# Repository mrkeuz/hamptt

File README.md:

Ham PTT
=======

Bluetooth PTT switch for ham radio transmitters like Baofeng UV-5R.  
Board helps to control transmitter from PC.

Motivation
----------

Testing of UART interface showed unstable connection. During transmit via UART an usb-ttl 
chip periodically crashes and stops working. Cause is some radio strong interference 
on USB cable. So Bluetooth serial protocol stack (SSP) chosen instead.

Schematic
---------

Host -> (Bluetooth) -> Esp-32 Arduino -> Relay -> Transmitter PTT button

* Hardware

    - Host PC with Bluetooth (tested Ubuntu 20.04)
    - Esp32 DevKit v1 (or similar esp32)
    - Relay shield
    - Baofeng UV-5R

Examples
--------

- Find BT devices `hcitool scan`
- Python

```python3
from hamptt import open_ptt

with open_ptt(bt_addr="A0:B1:C2:D3:E4:F5") as ptt:
    ptt.begin()
    # I.e. play message to transmitter or something else
    ptt.end()
```

Install
-------

* Host PC machine

    - Python 3.8
    - Bluetooth's libs (required for pybluez)

      ```shell
      sudo apt-get install bluez libbluetooth-dev
      ```

    - Pip
      ```shell
      python3 -m pip install "hamptt[bt]"
      ```

* Esp32

    - Upload sketch to your esp-32 via PlatformIO  
      NOTE! Check your board config in `platformio.ini` (see: https://platformio.org/)
      ```
      pio run -t upload
      ``` 

    - Connect pins Esp-32 to relay

        - VVC -> Relay +
        - GND -> Relay -
        - GPIO D25 -> Relay IN

    - Connect relay and audio, for Baofeng UV-5R it looks like:

      NOTE: You can rebuild your hands-free cable or buy another one

Development
===========

* Build and install
  ```shell
  pip3 uninstall hamptt
  rm -rf dist && poetry build && pip3 install ./dist/*.whl
  ```
  
* Publish
  - Prepare  
     ```shell
    poetry config repositories.testpypi https://test.pypi.org/legacy/
    poetry config pypi-token.testpypi <TOKEN>
    
    poetry config repositories.pypi https://upload.pypi.org/legacy/
    poetry config pypi-token.pypi <TOKEN>
    ```  
  
  - Publish
    ```shell
    poetry publish --build -r testpypi
    
    poetry publish --build -r pypi
    ````

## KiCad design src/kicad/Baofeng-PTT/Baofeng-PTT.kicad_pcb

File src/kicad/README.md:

Esp32 PTT HAT
=============

PTT where using darlington array fot PTT instead relay. Compatible with `ESP32 WROOM DevKit v1` board

Screenshots
-----------

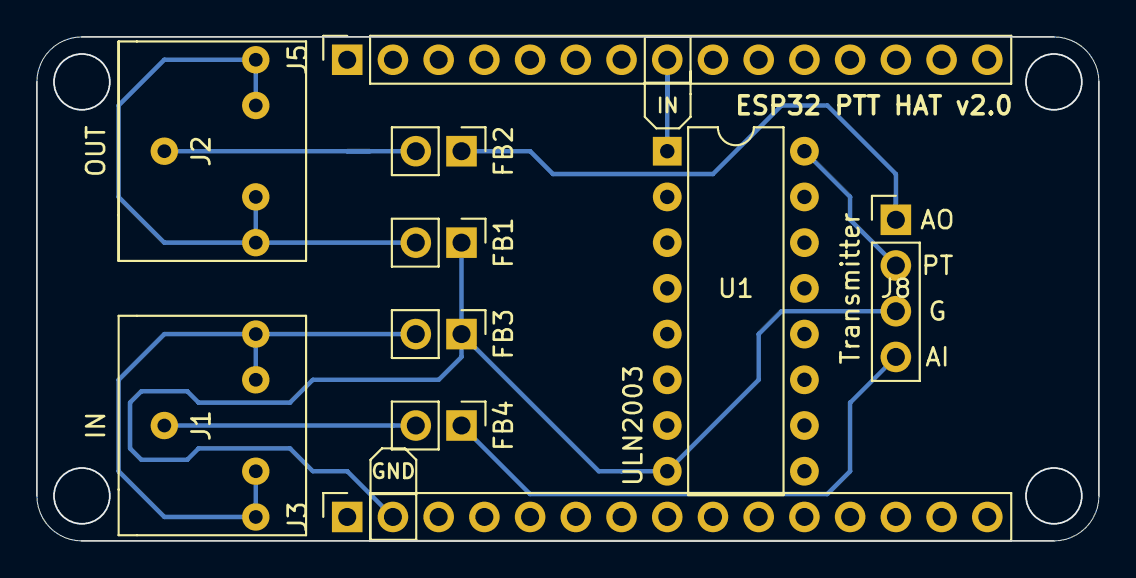
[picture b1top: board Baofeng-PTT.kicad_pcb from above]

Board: 2 copper layers, 59.0 x 28.0 mm, 10 parts (0 on the bottom side), 9 nets.

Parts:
FB1, FB2, FB3, FB4: Ferrite_Bead; PinHeader_1x02_P2.54mm_Vertical
J1: IN; Audio_5conn
J2: OUT; Audio_5conn
J3: Conn_01x15; PinSocket_1x15_P2.54mm_Vertical
J5: Esp32; PinSocket_1x15_P2.54mm_Vertical
J8: Transmitter; PinHeader_1x04_P2.54mm_Vertical
U1: ULN2003; DIP-16_W7.62mm

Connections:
AI: FB4.1, J8.4
AO: FB2.1, J8.1
D25: J5.8, U1.1
GND: FB1.1, FB3.1, J3.2, J8.3, U1.8
unnamed: FB1.2, J2.R, J2.S
unnamed: FB2.2, J2.T
unnamed: FB3.2, J1.R, J1.S
unnamed: FB4.2, J1.T
PT: J8.2, U1.16

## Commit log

2020-06-24 Change README.rst and CHANGELOG.rst
    Add links for python install
    Fix typos
    Change changelog
2020-06-24 Fix code style
    Flake8 fixes
2021-07-09 Next version of pcb
    Reduce size of pcb
2021-07-09 Add new pcb for exclude relay module and to add audio normalize
    Replace relay module to ULN2003 switch
    Add in/out audio level normalizer
2021-07-09 Add watchdogs for BT connection
2021-07-09 Add ping support for BT PTT for speed-up connection
2021-07-11 Change readme
2021-07-11 Cleanup project
2021-07-11 Add PlatformIO support
2021-07-11 Fix typo
2021-07-17 Fix gpio in readme
2021-07-17 Fix stopTx() regression
2021-07-17 Add autoclose in end of with clause
2021-07-18 Change readme. Minor refactoring
2021-07-18 Cleanup kikad
2021-07-18 Cleanup Kikad project
2021-07-18 Minor refactoring arduino
2021-07-18 Fix typos in code
2021-07-18 Move kikad project to src folder
2021-07-18 Replace `setup.py` to poetry
2021-07-18 Change README.md
2021-07-18 Fix urls
2021-07-18 Update images
2021-07-18 Minor PCB changing
2021-07-20 Fix dependencies. Bump version.
2021-07-20 Remove unnecessary files
2021-08-12 Minor change pcb
